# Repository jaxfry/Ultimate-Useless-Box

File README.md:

[![Stargazers][stars-shield]][stars-url]
[![Issues][issues-shield]][issues-url]
[![project_license][license-shield]][license-url]

<!-- PROJECT LOGO -->
<br />
<div align="center">

<h3 align="center">Ultimate Useless Box</h3>

  <p align="center">
    The Ultimate Useless Box, a box that does nothing, with style.
    <br />
    <br />
    <a href="#gallery--renders">View Renders</a>
    &middot;
    <a href="#custom-pcb">View PCB</a>
  </p>
</div>

<!-- TABLE OF CONTENTS -->
<details>
  <summary>Table of Contents</summary>
  <ol>
    <li>
      <a href="#about-the-project">About The Project</a>
      <ul>
        <li><a href="#built-with">Built With</a></li>
      </ul>
    </li>
    <li>
      <a href="#gallery--renders">Gallery & Renders</a>
    </li>
    <li>
      <a href="#custom-pcb">Custom PCB</a>
    </li>
    <li><a href="#bill-of-materials">Bill of Materials</a></li>
    <li><a href="#license">License</a></li>
  </ol>
</details>

<!-- ABOUT THE PROJECT -->
## About The Project

While most useless boxes just flip a switch, this one has personality. Powered by an **ESP32-S3**, this box uses a Time-of-Flight sensor to detect your hand before you even push the swtich, allowing the box to react by driving away, with the OLED screen, or countless other ways!
This project is heavily inspired by LuuMa EV3.
When I saw that video many years ago, I realized I wanted my own useless box. Then I realized that Lego Mindstorm kits are prohibitively expensive. Many years later and I decided to make my own using standard electronic components with a few unique twists of my own :)

**Key Features:**
* **OLED Display** for animated faces.
* **Fun Built in Power Management:** Mainly for learning and fun but we charge over usb-C!
* **Wheels** for driving away.
* **TOF** sensor for detecting hands.
* **A Retractable Switch**
<p align="right">(<a href="#readme-top">back to top</a>)</p>

### Built With

*   
*   
*   
*   

<p align="right">(<a href="#readme-top">back to top</a>)</p>

### Custom PCB
<div align="center">

</div>

<!-- GALLERY -->
<h2 id="gallery--renders">Gallery & Renders</h2>

<div align="center">

</div>

<p align="right">(<a href="#readme-top">back to top</a>)</p>

### Project Goals
- Build a reliable useless box with some personality
- Use accessible parts and open files
- Learn more about PCB design

## How to build
It should be pretty easy, the PCB has labeled connectors for what you need to plug in where. Basically, plug the servos into the headers labeled servos, the motors into the ports labeled motor right and motor left, the TOF sensor into TOF and switch into Switch, and you should be good to go.

<p align="right">(<a href="#readme-top">back to top</a>)</p>

<!-- MARKDOWN LINKS & IMAGES -->
<!-- https://www.markdownguide.org/basic-syntax/#reference-style-links -->
[stars-shield]: https://img.shields.io/github/stars/jaxfry/Ultimate-Useless-Box.svg?style=for-the-badge
[stars-url]: https://github.com/jaxfry/Ultimate-Useless-Box/stargazers
[issues-shield]: https://img.shields.io/github/issues/jaxfry/Ultimate-Useless-Box.svg?style=for-the-badge
[issues-url]: https://github.com/jaxfry/Ultimate-Useless-Box/issues
[license-shield]: https://img.shields.io/github/license/jaxfry/Ultimate-Useless-Box.svg?style=for-the-badge
[license-url]: https://github.com/jaxfry/Ultimate-Useless-Box/blob/main/LICENSE.txt

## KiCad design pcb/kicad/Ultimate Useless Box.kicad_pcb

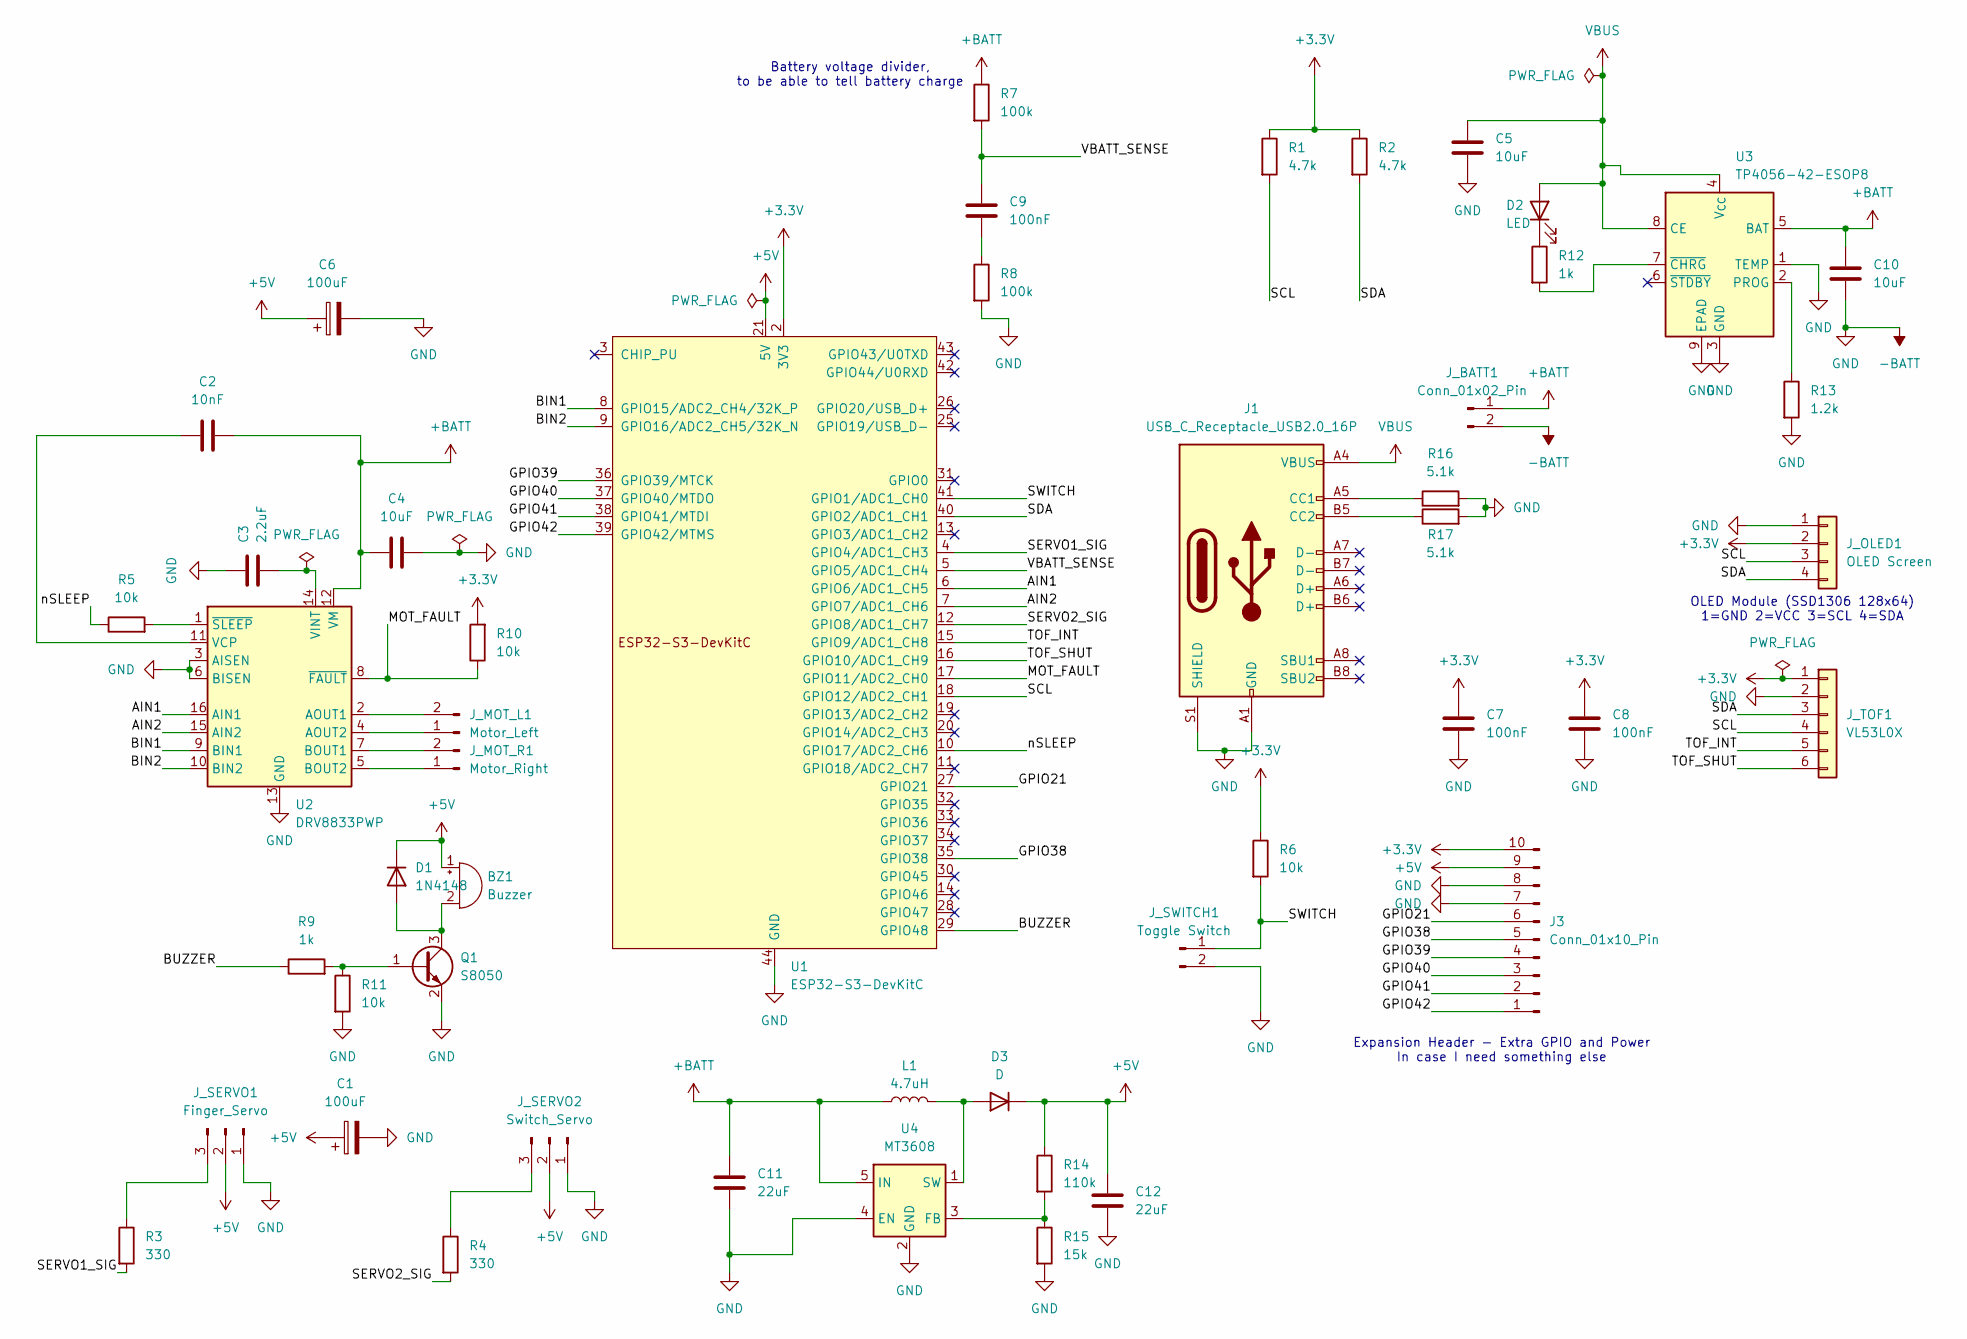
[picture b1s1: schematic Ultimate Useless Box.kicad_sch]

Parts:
BZ1: Buzzer; Buzzer_12x9.5RM7.6
C1, C6: 100uF; CP_Radial_D8.0mm_P3.50mm
C2: 10nF; C_0805_2012Metric
C3: 2.2uF; C_0805_2012Metric
C4, C5, C10: 10uF; C_0805_2012Metric
C7, C8, C9: 100nF; C_0805_2012Metric
C11, C12: 22uF; C_0805_2012Metric
D1: 1N4148; D_SOD-323
D2: LED; LED_D5.0mm
D3: D; D_SMA
J1: USB_C_Receptacle_USB2.0_16P; USB_C_Receptacle_HRO_TYPE-C-31-M-12
J3: Conn_01x10_Pin; PinHeader_1x10_P2.54mm_Vertical
J_BATT1: Conn_01x02_Pin; JST_PH_B2B-PH-K_1x02_P2.00mm_Vertical
J_MOT_L1: Motor_Left; JST_PH_B2B-PH-K_1x02_P2.00mm_Vertical
J_MOT_R1: Motor_Right; JST_PH_B2B-PH-K_1x02_P2.00mm_Vertical
J_OLED1: OLED Screen; JST_PH_B4B-PH-K_1x04_P2.00mm_Vertical
J_SERVO1: Finger_Servo; PinHeader_1x03_P2.54mm_Vertical
J_SERVO2: Switch_Servo; PinHeader_1x03_P2.54mm_Vertical
J_SWITCH1: Toggle Switch; JST_PH_B2B-PH-K_1x02_P2.00mm_Vertical
J_TOF1: VL53L0X; JST_PH_B6B-PH-K_1x06_P2.00mm_Vertical
L1: 4.7uH; L_Taiyo-Yuden_NR-40xx
Q1: S8050; SOT-23
R1, R2: 4.7k; R_0805_2012Metric
R3, R4: 330; R_0805_2012Metric
R5, R6, R10, R11: 10k; R_0805_2012Metric
R7, R8: 100k; R_0805_2012Metric
R9, R12: 1k; R_0805_2012Metric
R13: 1.2k; R_0805_2012Metric
R14: 110k; R_0805_2012Metric
R15: 15k; R_0805_2012Metric
R16, R17: 5.1k; R_0805_2012Metric
U1: ESP32-S3-DevKitC
U2: DRV8833PWP; HTSSOP-16-1EP_4.4x5mm_P0.65mm_EP3.4x5mm_Mask2.46x2.31mm_The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
U3: TP4056-42-ESOP8; SOIC-8-1EP_3.9x4.9mm_P1.27mm_EP2.41x3.3mm_ThermalVias
U4: MT3608; SOT-23-6

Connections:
+3.3V: C7.1, C8.1, J3.10, J_OLED1.2, J_TOF1.1, R1.1, R2.1, R6.1, R10.2, U1.1 (3V3), U1.2 (3V3)
+5V: BZ1.1 (+), C1.1, C6.1, C12.1, D1.1 (K), D3.1 (K), J3.9, J_SERVO1.2, J_SERVO2.2, R14.1, U1.21 (5V)
+BATT: C2.2, C4.1, C10.1, C11.1, J_BATT1.1, L1.1, R7.1, U2.12 (VM), U3.5 (BAT), U4.5 (IN)
-BATT: C1.2, C3.1, C4.2, C5.1, C6.2, C7.2, C8.2, C10.2, C11.2, C12.2, J1.A1 (GND), J1.A12 (GND), J1.B1 (GND), J1.B12 (GND), J1.S1 (SHIELD), J3.7, J3.8, J_BATT1.2, J_OLED1.1, J_SERVO1.1, J_SERVO2.1, J_SWITCH1.2, J_TOF1.2, Q1.2 (E), R8.2, R11.2, R13.2, R15.2, R16.2, R17.2, U1.22 (GND), U1.23 (GND), U1.24 (GND), U1.44 (GND), U2.3 (AISEN), U2.6 (BISEN), U2.13 (GND), U2.17 (GND), U3.1 (TEMP), U3.3 (GND), U3.9 (EPAD), U4.2 (GND), U4.4 (EN)
/AIN1: U1.6 (GPIO6/ADC1_CH5), U2.16 (AIN1)
/AIN2: U1.7 (GPIO7/ADC1_CH6), U2.15 (AIN2)
/BIN1: U1.8 (GPIO15/ADC2_CH4/32K_P), U2.9 (BIN1)
/BIN2: U1.9 (GPIO16/ADC2_CH5/32K_N), U2.10 (BIN2)
/BUZZER: R9.1, U1.29 (GPIO48)
/GPIO21: J3.6, U1.27 (GPIO21)
/GPIO38: J3.5, U1.35 (GPIO38)
/GPIO39: J3.4, U1.36 (GPIO39/MTCK)
/GPIO40: J3.3, U1.37 (GPIO40/MTDO)
/GPIO41: J3.2, U1.38 (GPIO41/MTDI)
/GPIO42: J3.1, U1.39 (GPIO42/MTMS)
/MOT_FAULT: R10.1, U1.17 (GPIO11/ADC2_CH0), U2.8 (~FAULT)
/SCL: J_OLED1.3, J_TOF1.4, R1.2, U1.18 (GPIO12/ADC2_CH1)
/SDA: J_OLED1.4, J_TOF1.3, R2.2, U1.40 (GPIO2/ADC1_CH1)
/SERVO1_SIG: R3.2, U1.4 (GPIO4/ADC1_CH3)
/SERVO2_SIG: R4.2, U1.12 (GPIO8/ADC1_CH7)
/SWITCH: J_SWITCH1.1, R6.2, U1.41 (GPIO1/ADC1_CH0)
/TOF_INT: J_TOF1.5, U1.15 (GPIO9/ADC1_CH8)
/TOF_SHUT: J_TOF1.6, U1.16 (GPIO10/ADC1_CH9)
/VBATT_SENSE: C9.1, R7.2, U1.5 (GPIO5/ADC1_CH4)
/nSLEEP: R5.1, U1.10 (GPIO17/ADC2_CH6)
unnamed: BZ1.2 (-), D1.2 (A), Q1.3 (C)
unnamed: C9.2, R8.1
unnamed: D2.1 (K), R12.1
unnamed: D3.2 (A), L1.2, U4.1 (SW)
unnamed: J1.A5 (CC1), R16.1
unnamed: J1.B5 (CC2), R17.1
unnamed: J_MOT_L1.1, U2.4 (AOUT2)
unnamed: J_MOT_L1.2, U2.2 (AOUT1)
unnamed: J_MOT_R1.1, U2.5 (BOUT2)
unnamed: J_MOT_R1.2, U2.7 (BOUT1)
unnamed: J_SERVO1.3, R3.1
unnamed: J_SERVO2.3, R4.1
unnamed: Q1.1 (B), R9.2, R11.1
unnamed: C2.1, U2.11 (VCP)
unnamed: C3.2, U2.14 (VINT)
unnamed: R5.2, U2.1 (~SLEEP)
unnamed: R13.1, U3.2 (PROG)
unnamed: R12.2, U3.7 (~CHRG)
unnamed: R14.2, R15.1, U4.3 (FB)
VBUS: C5.2, D2.2 (A), J1.A4 (VBUS), J1.A9 (VBUS), J1.B4 (VBUS), J1.B9 (VBUS), U3.4 (V_{CC}), U3.8 (CE)

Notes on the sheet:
Battery voltage divider, to be able to tell battery charge
Expansion Header - Extra GPIO and Power In case I need something else
OLED Module (SSD1306 128x64) 1=GND 2=VCC 3=SCL 4=SDA

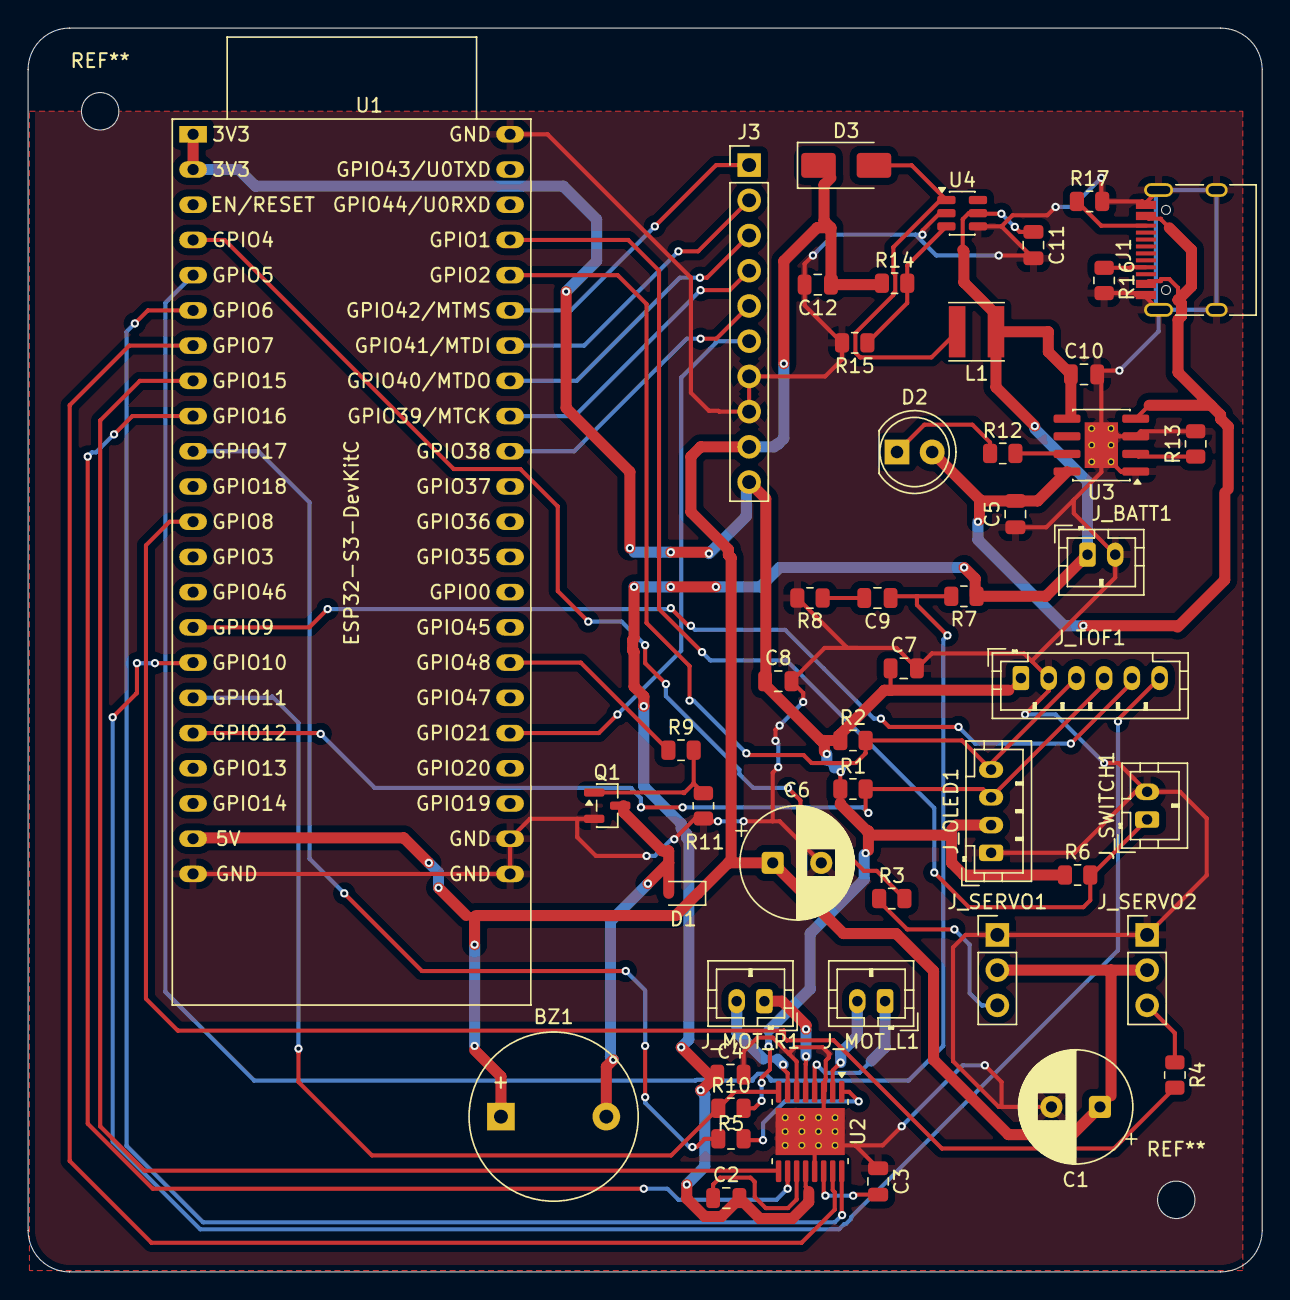
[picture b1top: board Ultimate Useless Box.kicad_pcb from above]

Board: 2 copper layers, 89.0 x 89.7 mm, 49 parts (0 on the bottom side), 45 nets.

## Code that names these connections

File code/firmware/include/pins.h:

#pragma once

#include <Arduino.h>

// Inputs
constexpr uint8_t PIN_MAIN_SWITCH = 1;
constexpr uint8_t PIN_VBATT_SENSE = 5;

// I2C bus shared by OLED and ToF.
constexpr uint8_t PIN_I2C_SDA = 2;
constexpr uint8_t PIN_I2C_SCL = 12;

// ToF control lines.
constexpr uint8_t PIN_TOF_SHUT = 10;

// Servo outputs.
constexpr uint8_t PIN_SERVO_1 = 4;
constexpr uint8_t PIN_SERVO_2 = 8;

// DRV8833 control.
constexpr uint8_t PIN_MOT_NSLEEP = 17;

constexpr uint8_t PIN_MOT_AIN1 = 6;
constexpr uint8_t PIN_MOT_AIN2 = 7;

constexpr uint8_t PIN_MOT_BIN1 = 15;
constexpr uint8_t PIN_MOT_BIN2 = 16;

// Audio output.
constexpr uint8_t PIN_BUZZER = 48;

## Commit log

2026-03-06 setup structure
2026-03-11 Refactor code structure for improved readability and maintainability
2026-03-12 add GPIO headers, wire sensor
2026-03-13 Finish schematic
2026-03-22 Finish Kicad
2026-04-07 Made changes
2026-04-23 Update CAD and all of the code
2026-04-28 add readme and step files
2026-05-04 Update BOM & readme
2026-05-04 remove copy of BOM from readme
2026-05-06 update with schematic
